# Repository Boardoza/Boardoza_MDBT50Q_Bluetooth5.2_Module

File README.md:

# Boardoza MDBT50Q Bluetooth Module

The **Boardoza MDBT50Q Bluetooth Module** is a high-performance wireless communication module based on the **Raytac MDBT50Q** series, featuring the **Nordic Semiconductor nRF52833 SoC** and supporting **Bluetooth 5.2**. This compact and power-efficient module is designed for applications requiring robust, long-range, and low-power wireless connectivity — such as IoT devices, smart home products, wearables, and industrial sensors.

It offers a UART communication interface and flexible configuration options, including selectable RC oscillators and hardware flow control. The MDBT50Q ensures reliability and ease of integration for developers working on BLE-enabled projects.

## [Click here to purchase!](https://www.ozdisan.com/p/gelistirme-kitleri-ve-aksesuarlari-617/boardoza-boardoza-mdbt50q-1202711)

|Front Side|Back Side|
|:---:|:---:|
|||

---

## **Key Features**

- **Bluetooth 5.2 Support:** Enables high-speed, low-energy communication with extended range.  
- **Nordic nRF52833 SoC:** Built-in ARM® Cortex®-M4 CPU with FPU operating up to 64 MHz.  
- **Low Power Consumption:** Optimized for long battery life in portable or IoT devices.  
- **Flexible UART Interface:** Configurable enable/disable control and flow control options.  
- **Selectable Clock Source:** Supports external or internal 32.768 kHz RC oscillator.  
- **512 KB RAM:** Large memory for advanced BLE applications.  

---

## **Technical Specifications**

**Manufacturer:** Raytac Corporation  
**Model:** MDBT50Q  
**Core Chip:** Nordic nRF52833 SoC (ARM® Cortex®-M4F)  
**Input Voltage:** 3.3V  
**Voltage Input Type:** Standard 6-pin header (2.54mm pitch)  
**Communication Interface:** UART  
**Bluetooth Version:** 5.2 (Low Energy)  
**Flash Memory:** 512 KB  
**RAM:** 128 KB  
**Antenna:** Integrated PCB antenna  
**Operating Frequency:** 2.4 GHz ISM band  
**Operating Temperature:** -40°C ~ +85°C  
**Extended Operating Temperature:** -40°C ~ +105°C 
**Board Dimensions:** 40mm x 40mm  
**Functions:** Bluetooth Low Energy Wireless Module  

---

## **Board Pinout**

### **( J1 ) Power & UART Connector**

| Pin Number | Pin Name | Description |
|:---:|:---:|---|
| 1 | 3V3 | Positive Power Supply |
| 2 | UART_TX | UART Transmitter |
| 3 | UART_RX | UART Receiver |
| 4 | UART_CTS | CTS, Clear to Send |
| 5 | UART_RTS | RTS, Request to Send |
| 6 | GND | Ground |

### **( J2 ) Control Connector**

| Pin Number | Pin Name | Description |
|:---:|:---:|---|
| 1 | ADC | 10-bit ADC input, updated every 200ms |
| 2 | UART_PD | Active-high with internal pull-up to disable UART hardware (default: disabled) |
| 3 | FLASH_DEFAULT | Active-low (0.48s ≤ Low ≤ 1s) triggers system reset to default configuration |
| 4 | RESET | Active-low system hardware reset |
| 5 | WAKEUP | Wake-up control output from deep sleep mode |

---

## **Board Dimensions**

---

## **Step Files**

[Boardoza MDBT50Q.step](./assets/MDBT50Q%20Step.step)

---

## **Datasheet**

[Raytac MDBT50Q Datasheet.pdf](./assets/MDBT50Q%20Datasheet.pdf)

---

## **Version History**

- V1.0.0 - Initial Release

---

## **Support**

For technical questions or assistance, please contact **<support@boardoza.com>**

---

## **License**

Shield: [![CC BY-SA 4.0][cc-by-sa-shield]][cc-by-sa]

This work is licensed under a [Creative Commons Attribution-ShareAlike 4.0 International License][cc-by-sa].

[![CC BY-SA 4.0][cc-by-sa-image]][cc-by-sa]

[cc-by-sa]: http://creativecommons.org/licenses/by-sa/4.0/  
[cc-by-sa-image]: https://licensebuttons.net/l/by-sa/4.0/88x31.png  
[cc-by-sa-shield]: https://img.shields.io/badge/License-CC%20BY--SA%204.0-lightgrey.svg

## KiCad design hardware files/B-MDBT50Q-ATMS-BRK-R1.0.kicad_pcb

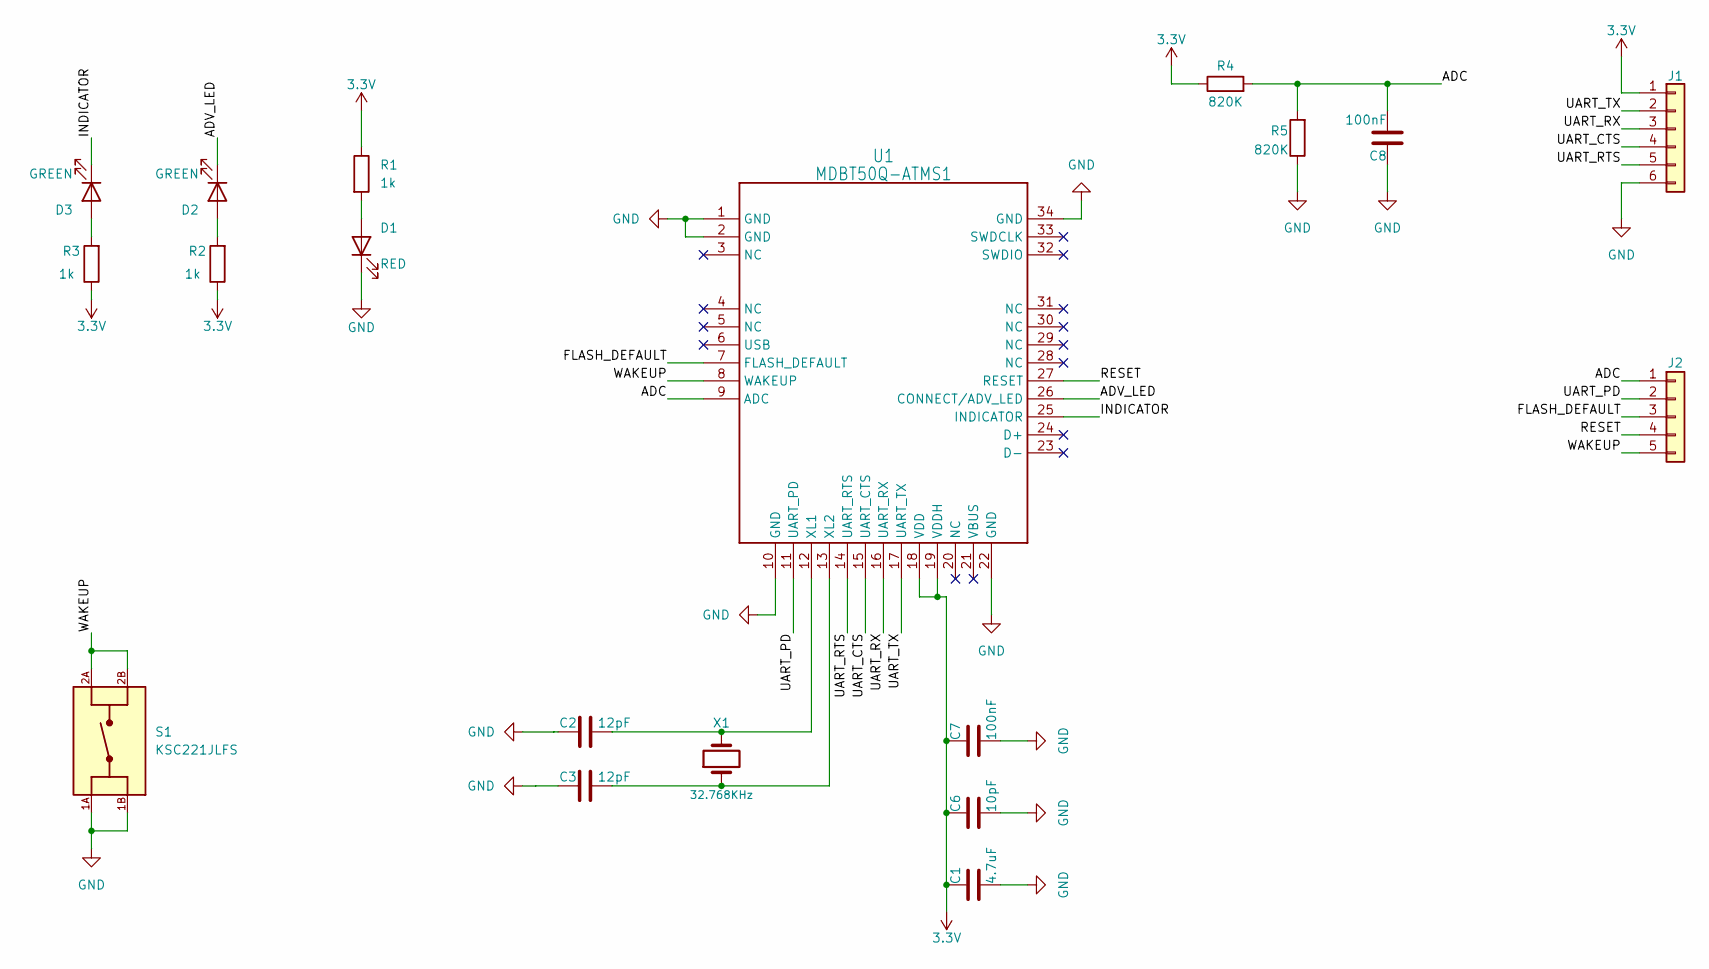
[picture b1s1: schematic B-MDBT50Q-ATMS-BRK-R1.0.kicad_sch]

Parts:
C1: 4.7uF; C_0603_1608Metric
C2, C3: 12pF; C_0603_1608Metric
C6: 10pF; C_0603_1608Metric
C7, C8: 100nF; C_0603_1608Metric
D1: RED; LED_0603_1608Metric
D2, D3: GREEN; LED_0603_1608Metric
J1: Conn_01x06; 2317-06S_1x06_P2.50mm_Vertical
J2: Conn_01x05; 2317-05S_1x05_P2.50mm_Vertical
R1, R2, R3: 1k; R_0603_1608Metric
R4, R5: 820K; R_0603_1608Metric
S1: KSC221JLFS; SW_KSC221JLFS; PARTREV 16 Mar 22
U1: MDBT50Q-ATMS1; MDBT50Q; MPN MDBT50Q-ATMS
X1: 32.768KHz; XTAL_CC7V-T1A-32.768K-9PF-20PPM-TB-QA; MPN FC-135 32.7680KA-AC3

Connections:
3.3V: C1.1, C6.1, C7.1, J1.1, R1.1, R2.1, R3.1, R4.1, U1.18 (VDD), U1.19 (VDDH)
/ADC: C8.2, J2.1, R4.2, R5.2, U1.9 (ADC)
/ADV_LED: D2.1 (K), U1.26 (CONNECT/ADV_LED)
/FLASH_DEFAULT: J2.3, U1.7 (FLASH_DEFAULT)
/INDICATOR: D3.1 (K), U1.25 (INDICATOR)
/RESET: J2.4, U1.27 (RESET)
/UART_CTS: J1.4, U1.15 (UART_CTS)
/UART_PD: J2.2, U1.11 (UART_PD)
/UART_RTS: J1.5, U1.14 (UART_RTS)
/UART_RX: J1.3, U1.16 (UART_RX)
/UART_TX: J1.2, U1.17 (UART_TX)
/WAKEUP: J2.5, S1.2A, S1.2B, U1.8 (WAKEUP)
GND: C1.2, C2.1, C3.1, C6.2, C7.2, C8.1, D1.1 (K), J1.6, R5.1, S1.1A, S1.1B, U1.1 (GND), U1.2 (GND), U1.10 (GND), U1.22 (GND), U1.34 (GND)
unnamed: D1.2 (A), R1.2
unnamed: D2.2 (A), R2.2
unnamed: D3.2 (A), R3.2
unnamed: C2.2, U1.12 (XL1), X1.2
unnamed: C3.2, U1.13 (XL2), X1.1

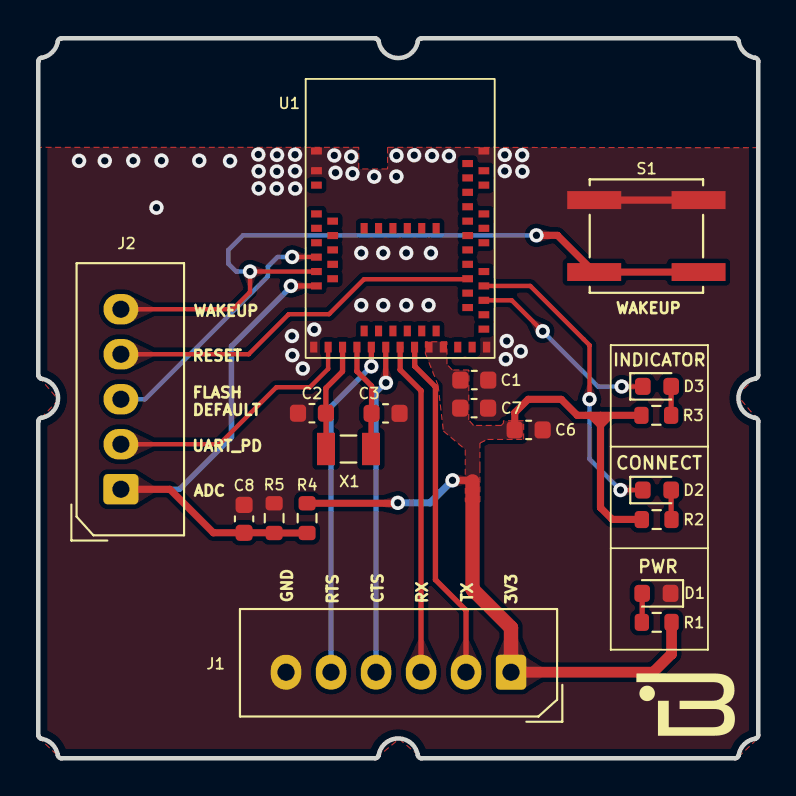
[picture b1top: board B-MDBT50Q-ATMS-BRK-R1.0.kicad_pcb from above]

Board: 2 copper layers, 40.0 x 40.0 mm, 19 parts (0 on the bottom side), 18 nets.

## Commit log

2025-11-17 Add MDBT50Q examples
